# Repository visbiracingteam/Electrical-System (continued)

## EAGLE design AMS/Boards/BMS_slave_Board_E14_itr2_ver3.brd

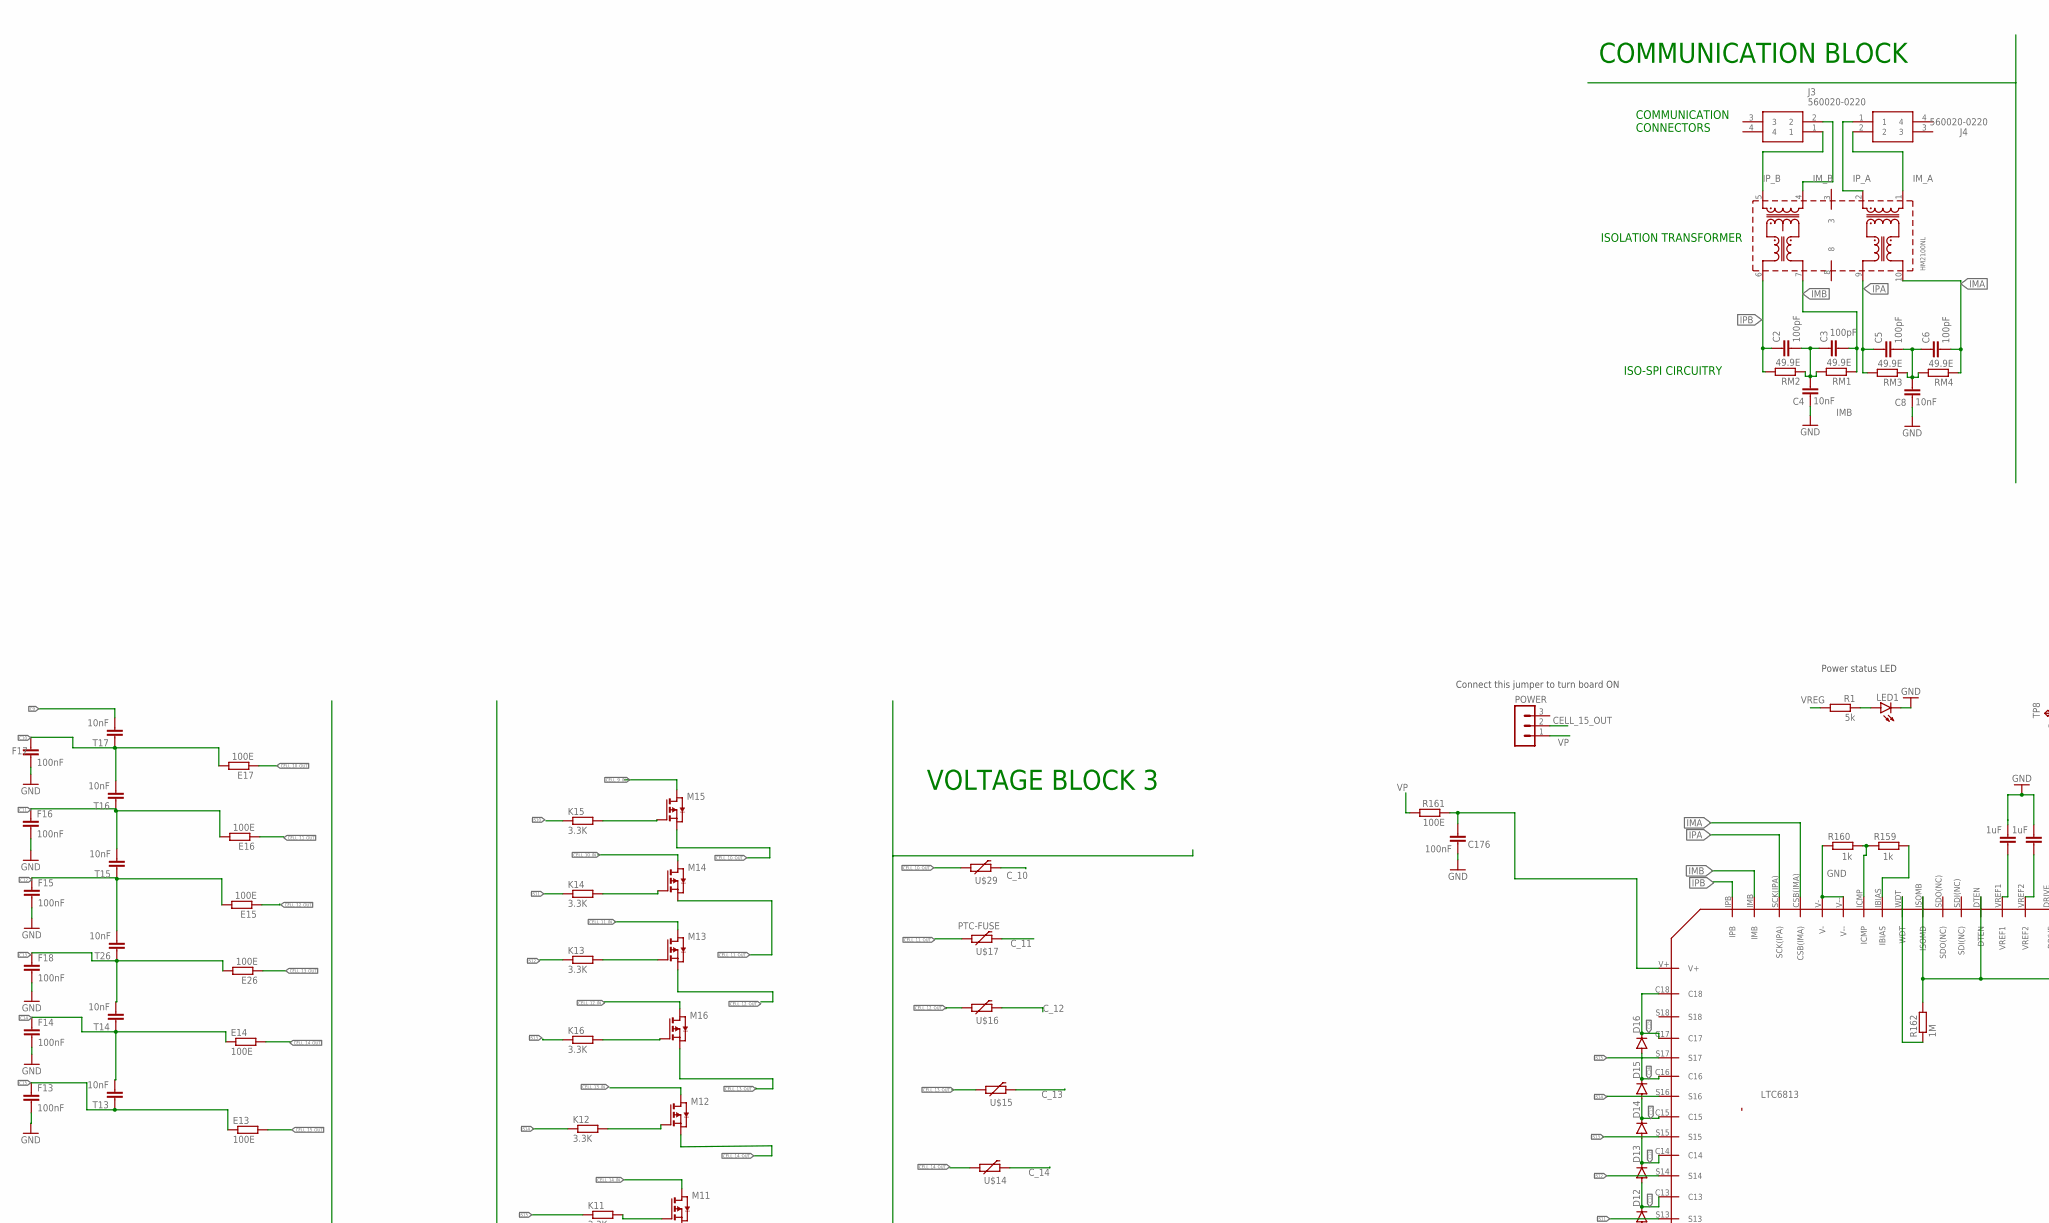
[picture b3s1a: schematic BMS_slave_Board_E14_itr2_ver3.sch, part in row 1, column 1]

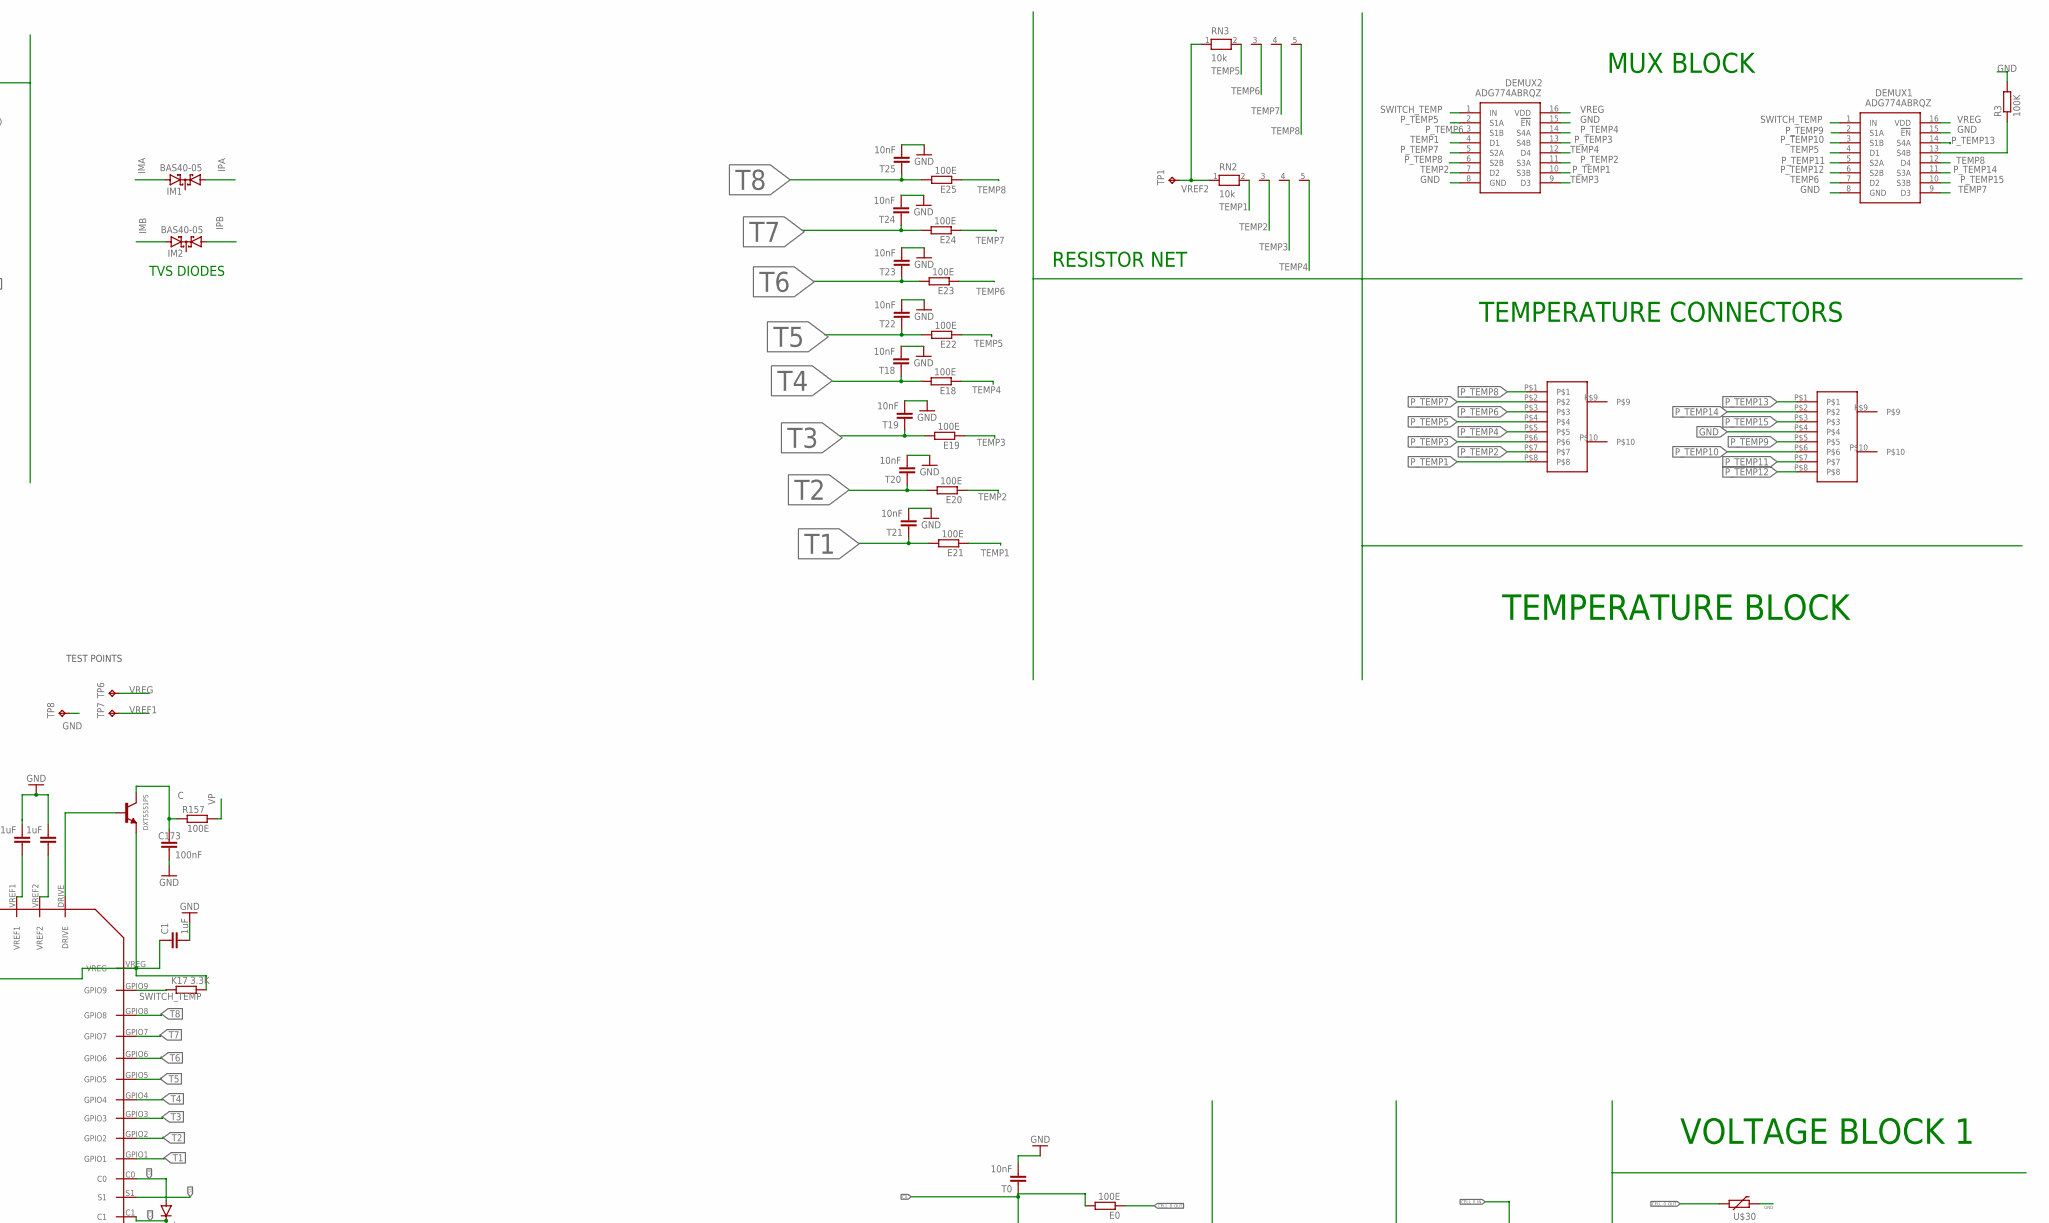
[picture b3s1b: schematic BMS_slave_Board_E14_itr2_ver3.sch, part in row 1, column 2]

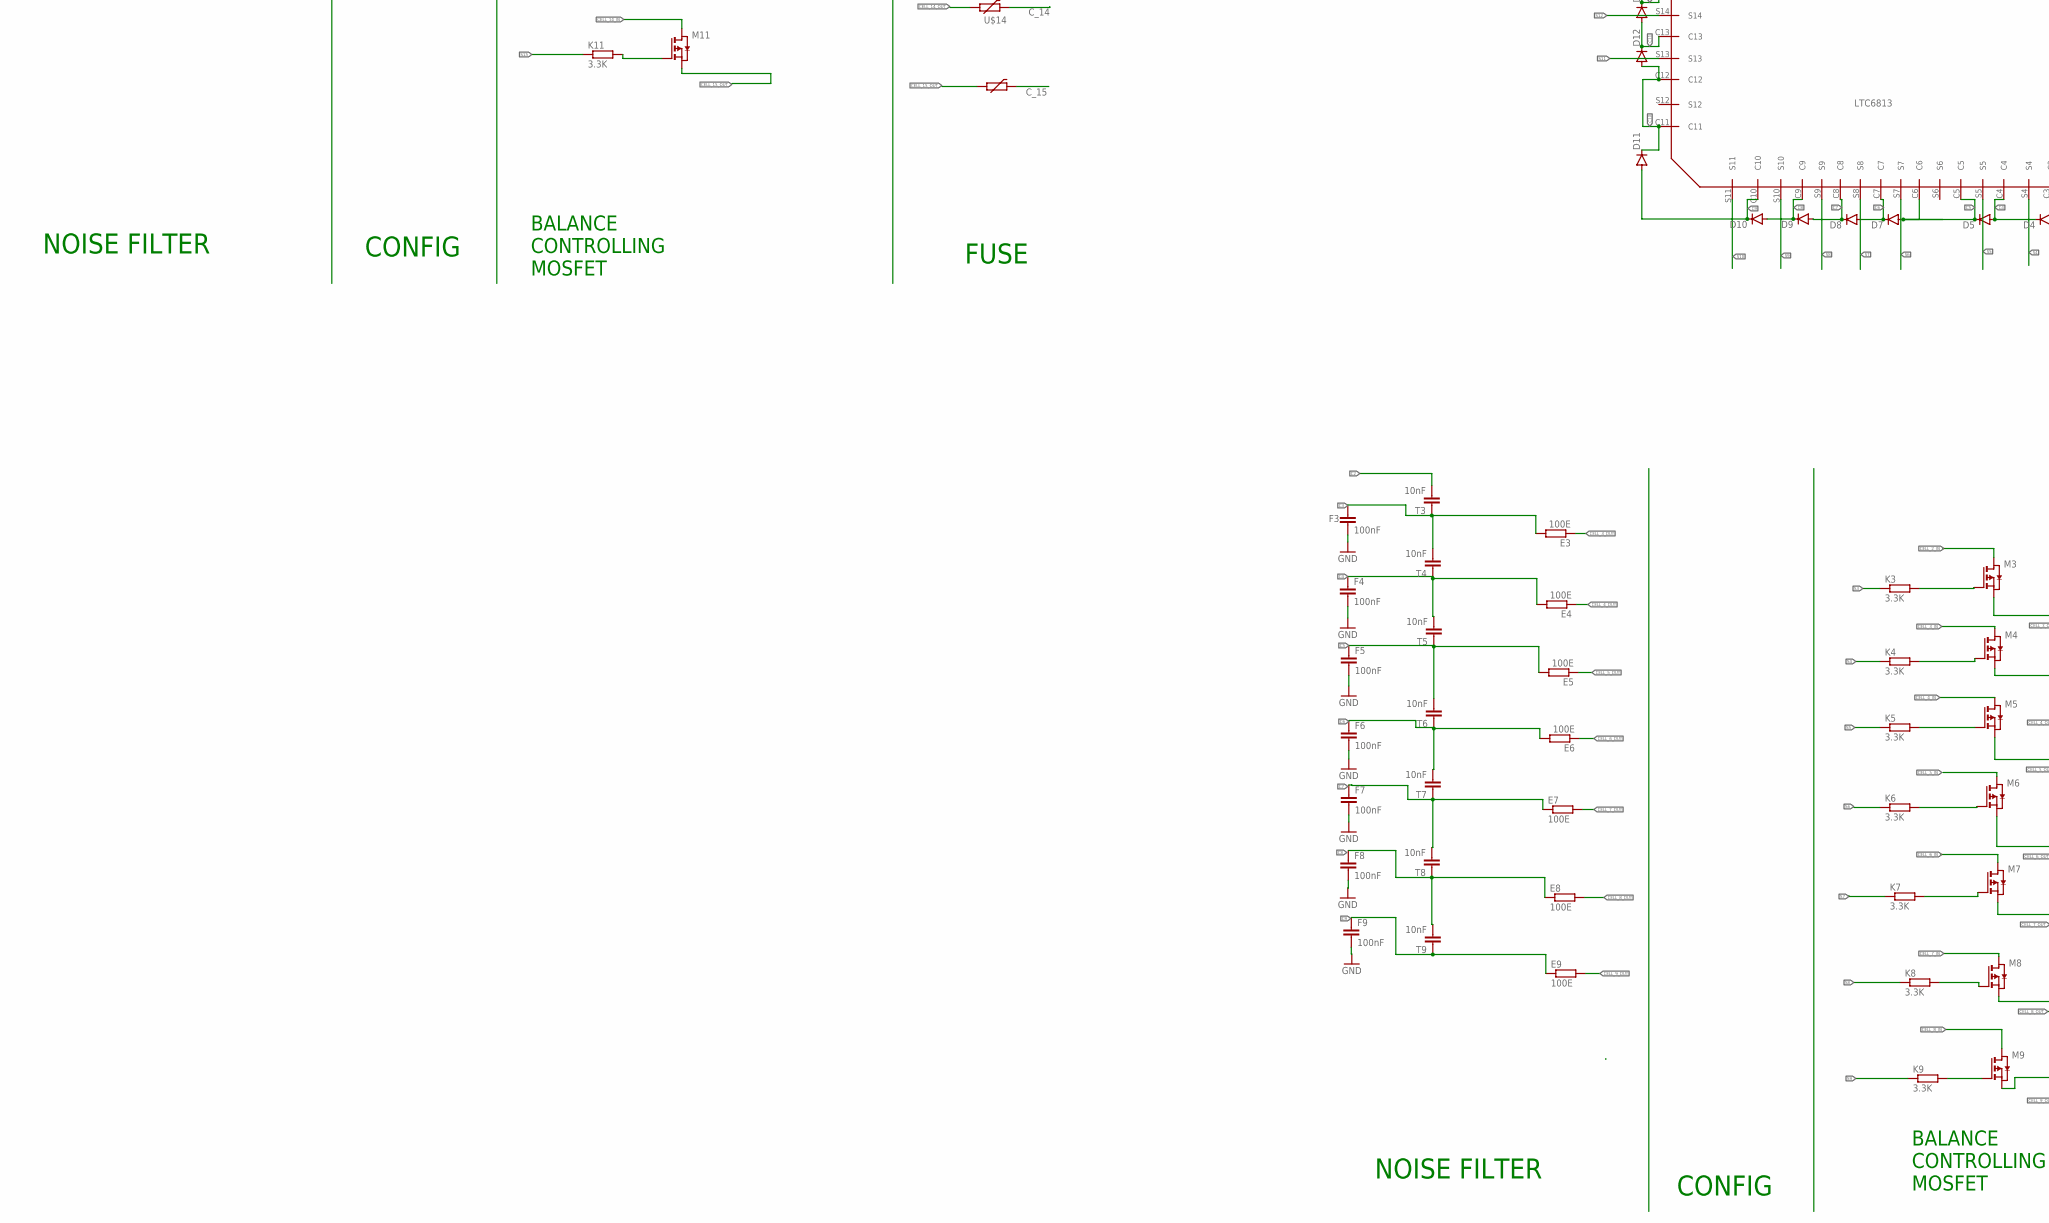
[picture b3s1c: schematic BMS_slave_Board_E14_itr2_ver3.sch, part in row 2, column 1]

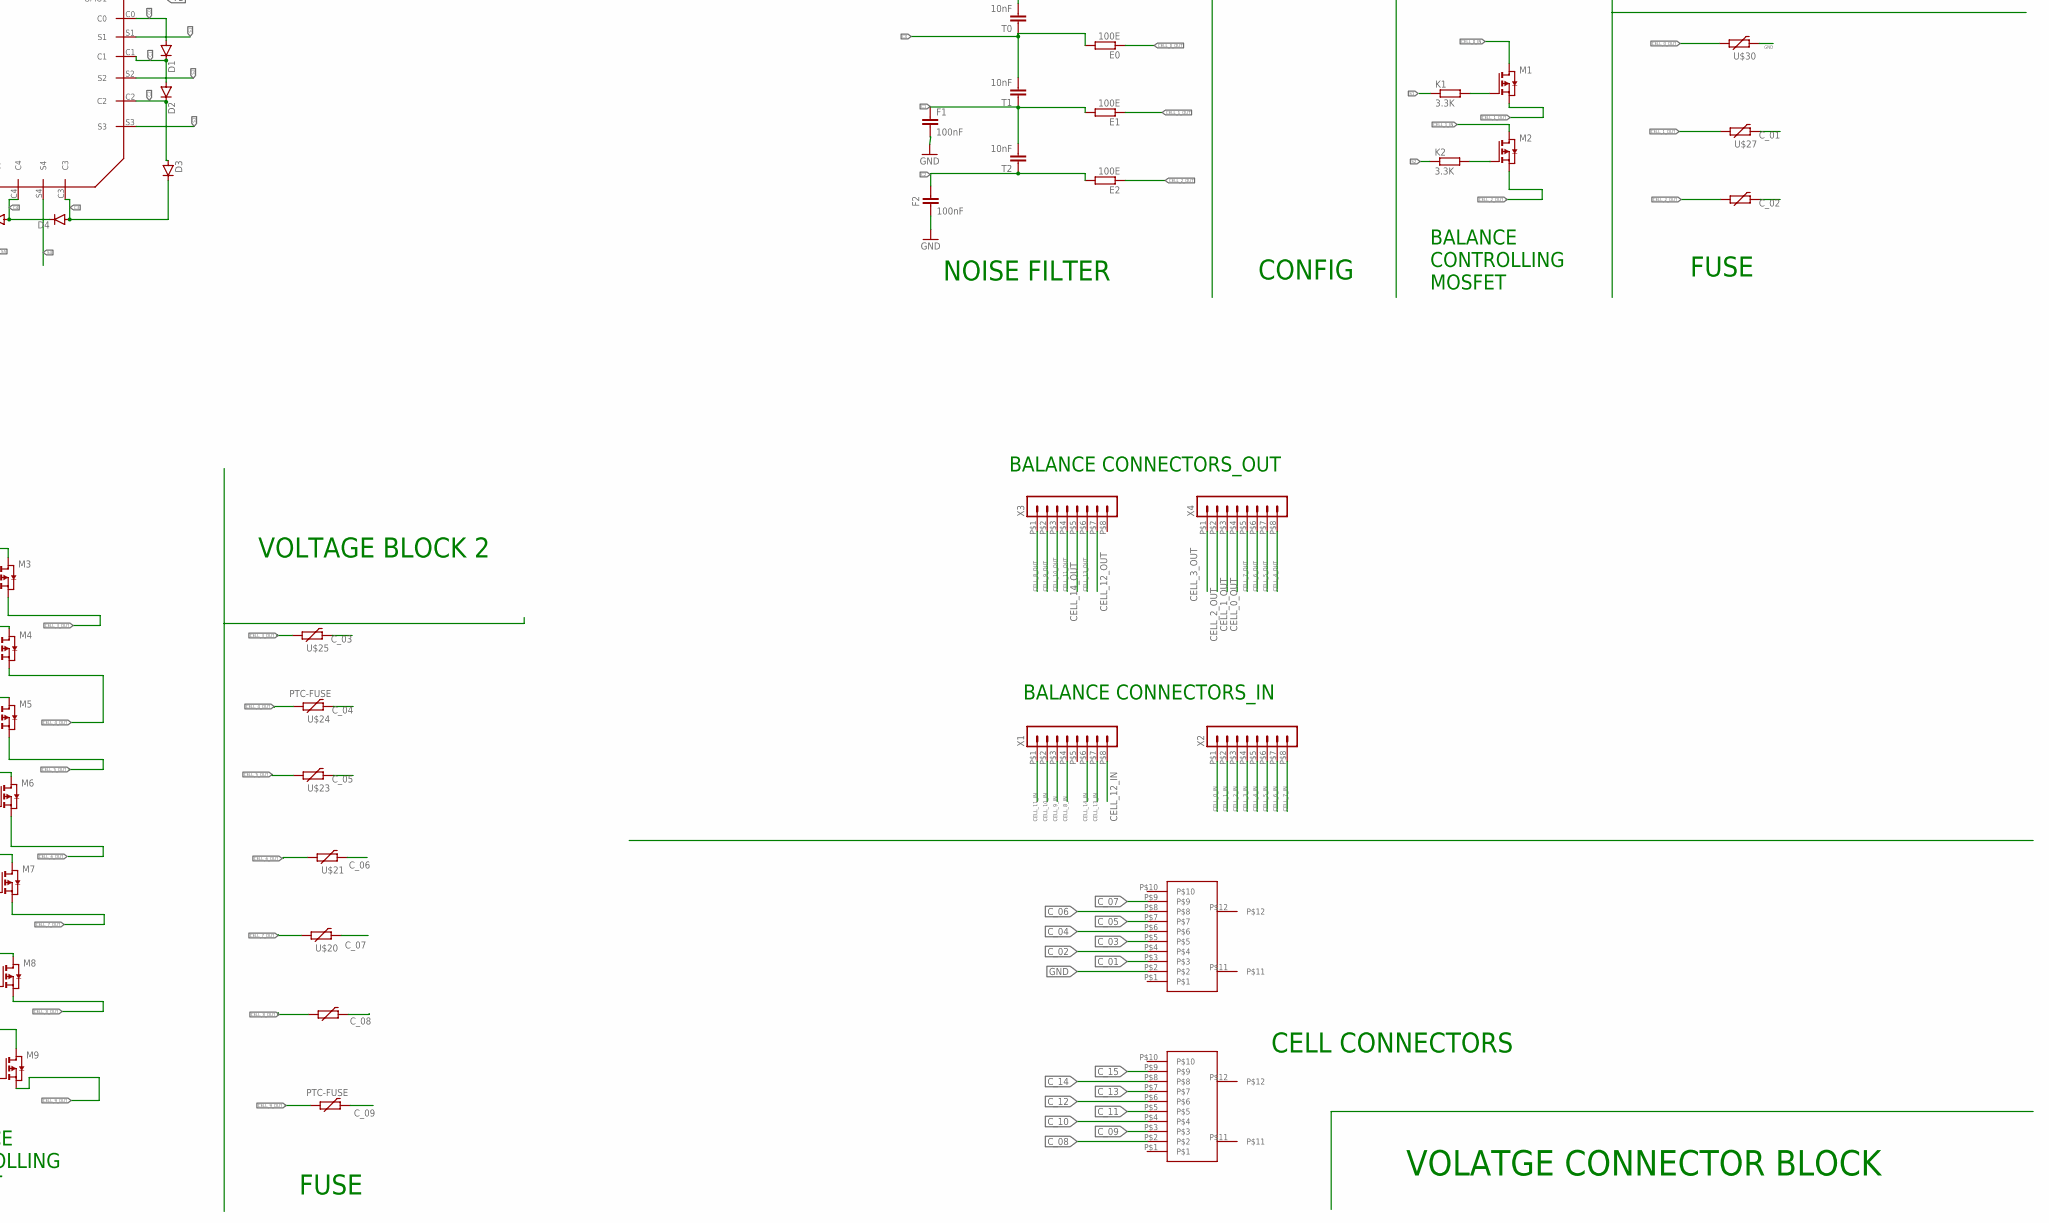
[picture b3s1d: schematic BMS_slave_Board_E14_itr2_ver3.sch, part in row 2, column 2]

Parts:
C1, C175, C177: 1uF; C0805
C2, C3, C5, C6: 100pF; C0603
C4, C8: 10nF; C0603
C173, C176: 100nF; C0805
D1, D2, D3, D4, D5, D7, D8, D9, D10, D11, D12, D13, D14, D15, D16: DIODE-SOD123; SOD123
DEMUX1, DEMUX2: ADG774ABRQZ; SOP64P600X175-16N
E0, E1, E2, E3, E4, E5, E6, E7, E8, E9, E13, E14, E15, E16, E17, E18, E19, E20, E21, E22, E23, E24, E25, E26: 100E; R0603
F1, F2, F3, F4, F5, F6, F7, F8, F9, F13, F14, F15, F16, F17, F18: 100nF; C1206
IM1, IM2: BAS40-05; SOT23
J3, J4: 560020-0220; 5600200220
K1, K2, K3, K4, K5, K6, K7, K8, K9, K11, K12, K13, K14, K15, K16, K17: 3.3K; R0603
LED1: LEDSMT1206; 1206
M1, M2, M3, M4, M5, M6, M7, M8, M9, M11, M12, M13, M14, M15, M16: PMOSSOT23; SOT-23
POWER: MA03-1
R1: 5k; R0805
R3: 100K; R0805
R157, R161: 100E; R0805
R159, R160: 1k; R0805
R162: 1M; R0805
RM1, RM2, RM3, RM4: 49.9E; R0603
RN2, RN3: 10k; RN-5
T0, T1, T2, T3, T4, T5, T6, T7, T8, T9, T13, T14, T15, T16, T17, T18, T19, T20, T21, T22, T23, T24, T25, T26: 10nF; C0603
TP1, TP6, TP7, TP8: TPPAD1-13; P1-13
U$1: HM2100NL
U$2: DXT5551P5
U$3: LTC6813
U$8, U$9: VERTICALBMS8
U$10, U$11: VERTICALBMS10
U$13, U$14, U$15, U$16, U$17, U$18, U$19, U$20, U$21, U$23, U$24, U$25, U$26, U$27, U$29, U$30: PTC-FUSE; 1206
X1, X2, X3, X4: HEADER_POS8_44914-0801; 44914-0801

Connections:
C: C173.1, R157.1, U$2.C
C0: D1.A, E0.2, T0.1, T1.2, U$3.C0
C1: D1.C, D2.A, E1.2, F1.1, T1.1, T2.2, U$3.C1
C2: D2.C, D3.A, E2.2, F2.1, T2.1, T3.2, U$3.C2
C3: D3.C, D4.A, E3.2, F3.1, T3.1, T4.2, U$3.C3
C4: D4.C, D5.A, E4.2, F4.1, T4.1, T5.2, U$3.C4
C5: D5.C, D7.A, E5.2, F5.1, T5.1, T6.2, U$3.C5, U$3.C6
C6: D7.C, D8.A, E6.2, F6.1, T6.1, T7.2, U$3.C7
C7: D8.C, D9.A, E7.1, F7.1, T7.1, T8.2, U$3.C8
C8: D9.C, D10.A, E8.1, F8.1, T8.1, T9.2, U$3.C9
C9: D10.C, D11.A, E9.1, F9.1, T9.1, T17.2, U$3.C10
C10: D11.C, D12.A, E17.2, F17.1, T16.2, T17.1, U$3.C11, U$3.C12
C11: D12.C, D13.A, E16.2, F16.1, T15.2, T16.1, U$3.C13
C12: D13.C, D14.A, E15.2, F15.1, T15.1, T26.2, U$3.C14
C13: D14.C, D15.A, E26.2, F18.1, T14.2, T26.1, U$3.C15
C14: D15.C, D16.A, E14.1, F14.1, T13.2, T14.1, U$3.C16
C15: D16.C, E13.1, F13.1, T13.1, U$3.C17, U$3.C18
CELL_0_IN: M1.1 (D), X2.P$1 (1)
CELL_0_OUT: E0.1, U$30.2, X4.P$4 (4)
CELL_1_IN: M2.1 (D), X2.P$2 (2)
CELL_1_OUT: E1.1, M1.2 (S), U$27.2, X4.P$3 (3)
CELL_2_IN: M3.1 (D), X2.P$3 (3)
CELL_2_OUT: E2.1, M2.2 (S), U$26.2, X4.P$2 (2)
CELL_3_IN: M4.1 (D), X2.P$4 (4)
CELL_3_OUT: E3.1, M3.2 (S), U$25.2, X4.P$1 (1)
CELL_4_IN: M5.1 (D), X2.P$5 (5)
CELL_4_OUT: E4.1, M4.2 (S), U$24.2, X4.P$8 (8)
CELL_5_IN: M6.1 (D), X2.P$6 (6)
CELL_5_OUT: E5.1, M5.2 (S), U$23.2, X4.P$7 (7)
CELL_6_IN: M7.1 (D), X2.P$7 (7)
CELL_6_OUT: E6.1, M6.2 (S), U$21.2, X4.P$6 (6)
CELL_7_IN: M8.1 (D), X2.P$8 (8)
CELL_7_OUT: E7.2, M7.2 (S), U$20.2, X4.P$5 (5)
CELL_8_IN: M9.1 (D), X1.P$4 (4)
CELL_8_OUT: E8.2, M8.2 (S), U$19.2, X3.P$1 (1)
CELL_9_IN: M15.1 (D), X1.P$3 (3)
CELL_9_OUT: E9.2, M9.2 (S), U$18.2, X3.P$2 (2)
CELL_10_IN: M14.1 (D), X1.P$2 (2)
CELL_10_OUT: E17.1, M15.2 (S), U$29.2, X3.P$3 (3)
CELL_11_IN: M13.1 (D), X1.P$1 (1)
CELL_11_OUT: E16.1, M14.2 (S), U$17.2, X3.P$4 (4)
CELL_12_IN: M16.1 (D), X1.P$8 (8)
CELL_12_OUT: E15.1, M13.2 (S), U$16.2, X3.P$7 (7)
CELL_13_IN: M12.1 (D), X1.P$7 (7)
CELL_13_OUT: E26.1, M16.2 (S), U$15.2, X3.P$6 (6)
CELL_14_IN: M11.1 (D), X1.P$6 (6)
CELL_14_OUT: E14.2, M12.2 (S), U$14.2, X3.P$5 (5)
CELL_15_OUT: E13.2, M11.2 (S), POWER.2, U$13.2
C_01: U$10.P$3, U$27.1
C_02: U$10.P$4, U$26.1
C_03: U$10.P$5, U$25.1
C_04: U$10.P$6, U$24.1
C_05: U$10.P$7, U$23.1
C_06: U$10.P$8, U$21.1
C_07: U$10.P$9, U$20.1
C_08: U$11.P$2, U$19.1
C_09: U$11.P$3, U$18.1
C_10: U$11.P$4, U$29.1
C_11: U$11.P$5, U$17.1
C_12: U$11.P$6, U$16.1
C_13: U$11.P$7, U$15.1
C_14: U$11.P$8, U$14.1
C_15: U$11.P$9, U$13.1
GND: C1.2, C4.1, C8.1, C173.2, C175.2, C176.2, C177.2, DEMUX1.8 (GND), DEMUX1.15 (!EN), DEMUX2.8 (GND), DEMUX2.15 (!EN), F1.2, F2.2, F3.2, F4.2, F5.2, F6.2, F7.2, F8.2, F9.2, F13.2, F14.2, F15.2, F16.2, F17.2, F18.2, LED1.C, R3.2, R160.1, T0.2, T18.2, T19.2, T20.2, T21.2, T22.2, T23.2, T24.2, T25.2, TP8.TP, U$3.V-, U$3.V--, U$9.P$4, U$10.P$2, U$30.1
IMA: C6.2, IM1.2 (A2), RM4.1, U$1.10, U$3.CSB(IMA)
IMB: C3.2, IM2.2 (A2), RM1.1, U$1.7, U$3.IMB
IM_A: J4.2, U$1.1
IM_B: J3.2, U$1.4
IPA: C5.1, IM1.1 (A1), RM3.2, U$1.9, U$3.SCK(IPA)
IPB: C2.1, IM2.1 (A1), RM2.2, U$1.6, U$3.IPB
IP_A: J4.1, U$1.2
IP_B: J3.1, U$1.5
unnamed: C2.2, C3.1, C4.2, RM1.2, RM2.1
unnamed: C5.2, C6.1, C8.2, RM3.1, RM4.2
unnamed: R162.1, U$3.WDT
unnamed: DEMUX1.13 (S4B), R3.1
unnamed: R159.1, R160.2, U$3.ICMP
unnamed: K1.2, M1.3 (G)
unnamed: K2.2, M2.3 (G)
unnamed: K3.2, M3.3 (G)
unnamed: K4.2, M4.3 (G)
unnamed: K5.2, M5.3 (G)
unnamed: K6.2, M6.3 (G)
unnamed: K7.2, M7.3 (G)
unnamed: K16.2, M16.3 (G)
unnamed: K8.2, M8.3 (G)
unnamed: K9.2, M9.3 (G)
unnamed: K12.2, M12.3 (G)
unnamed: K15.2, M15.3 (G)
unnamed: K14.2, M14.3 (G)
unnamed: K13.2, M13.3 (G)
unnamed: K11.2, M11.3 (G)
unnamed: U$2.B, U$3.DRIVE
unnamed: R159.2, U$3.IBIAS
unnamed: C176.1, R161.1, U$3.V+
P_TEMP1: DEMUX2.10 (S3B), U$8.P$8
P_TEMP2: DEMUX2.11 (S3A), U$8.P$7
P_TEMP3: DEMUX2.13 (S4B), U$8.P$6
P_TEMP4: DEMUX2.14 (S4A), U$8.P$5
P_TEMP5: DEMUX2.2 (S1A), U$8.P$4
P_TEMP6: DEMUX2.3 (S1B), U$8.P$3
P_TEMP7: DEMUX2.5 (S2A), U$8.P$2
P_TEMP8: DEMUX2.6 (S2B), U$8.P$1
P_TEMP9: DEMUX1.2 (S1A), U$9.P$5
P_TEMP10: DEMUX1.3 (S1B), U$9.P$6
P_TEMP11: DEMUX1.5 (S2A), U$9.P$7
P_TEMP12: DEMUX1.6 (S2B), U$9.P$8
P_TEMP13: DEMUX1.14 (S4A), U$9.P$1
P_TEMP14: DEMUX1.11 (S3A), U$9.P$2
P_TEMP15: DEMUX1.10 (S3B), U$9.P$3
R: LED1.A, R1.1
S1: K1.1, U$3.S1
S2: K2.1, U$3.S2
S3: K3.1, U$3.S3
S4: K4.1, U$3.S4
S5: K5.1, U$3.S5
S6: K6.1, U$3.S7
S7: K7.1, U$3.S8
S8: K8.1, U$3.S9
S9: K9.1, U$3.S10
S10: K15.1, U$3.S11
S11: K14.1, U$3.S13
S12: K13.1, U$3.S14
S13: K16.1, U$3.S15
S14: K12.1, U$3.S16
S15: K11.1, U$3.S17
SWITCH_TEMP: DEMUX1.1 (IN), DEMUX2.1 (IN), K17.1, U$3.GPIO9
T1: E21.2, T21.1, U$3.GPIO1
T2: E20.2, T20.1, U$3.GPIO2
T3: E19.2, T19.1, U$3.GPIO3
T4: E18.2, T18.1, U$3.GPIO4
T5: E22.2, T22.1, U$3.GPIO5
T6: E23.2, T23.1, U$3.GPIO6
T7: E24.2, T24.1, U$3.GPIO7
T8: E25.2, T25.1, U$3.GPIO8
TEMP1: DEMUX2.4 (D1), E21.1, RN2.2
TEMP2: DEMUX2.7 (D2), E20.1, RN2.3
TEMP3: DEMUX2.9 (D3), E19.1, RN2.4
TEMP4: DEMUX2.12 (D4), E18.1, RN2.5
TEMP5: DEMUX1.4 (D1), E22.1, RN3.2
TEMP6: DEMUX1.7 (D2), E23.1, RN3.3
TEMP7: DEMUX1.9 (D3), E24.1, RN3.4
TEMP8: DEMUX1.12 (D4), E25.1, RN3.5
VP: POWER.1, R157.2, R161.2
VREF1: C175.1, TP7.TP, U$3.VREF1
VREF2: C177.1, RN2.1, RN3.1, TP1.TP, U$3.VREF2
VREG: C1.1, DEMUX1.16 (VDD), DEMUX2.16 (VDD), K17.2, R1.2, R162.2, TP6.TP, U$2.E, U$3.DTEN, U$3.ISOMB (ISOMD), U$3.VREG

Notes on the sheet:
Power status LED
MUX BLOCK
TEMPERATURE BLOCK
RESISTOR NET
TEMPERATURE CONNECTORS
TVS DIODES
ISOLATION TRANSFORMER
COMMUNICATION CONNECTORS
ISO-SPI CIRCUITRY
COMMUNICATION BLOCK
VOLATGE CONNECTOR BLOCK
CELL CONNECTORS
BALANCE CONNECTORS_OUT
BALANCE CONNECTORS_IN
VOLTAGE BLOCK 1
FUSE
BALANCE CONTROLLING MOSFET
CONFIG
NOISE FILTER
VOLTAGE BLOCK 2
VOLTAGE BLOCK 3
Connect this jumper to turn board ON
TEST POINTS

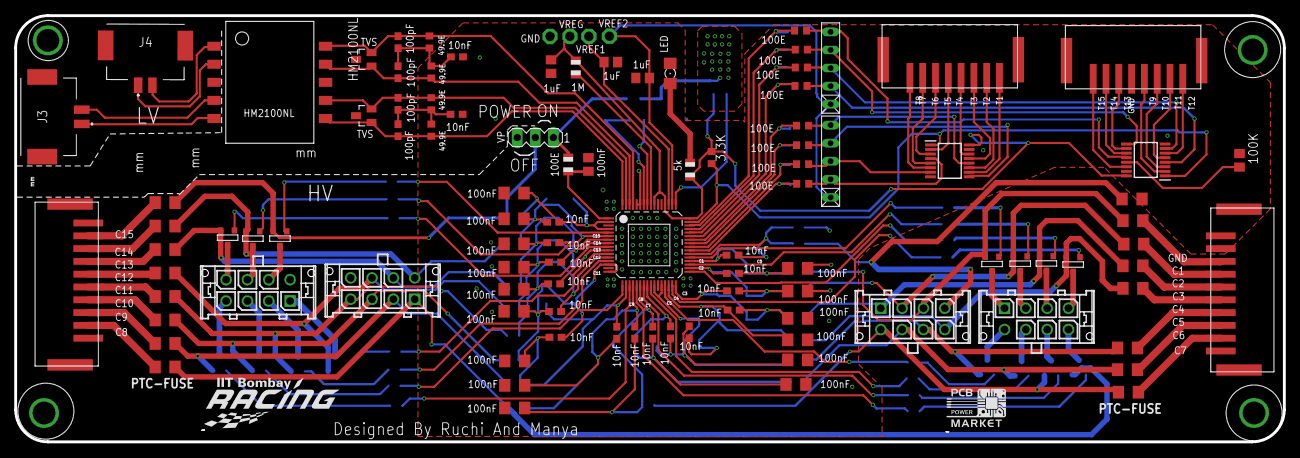
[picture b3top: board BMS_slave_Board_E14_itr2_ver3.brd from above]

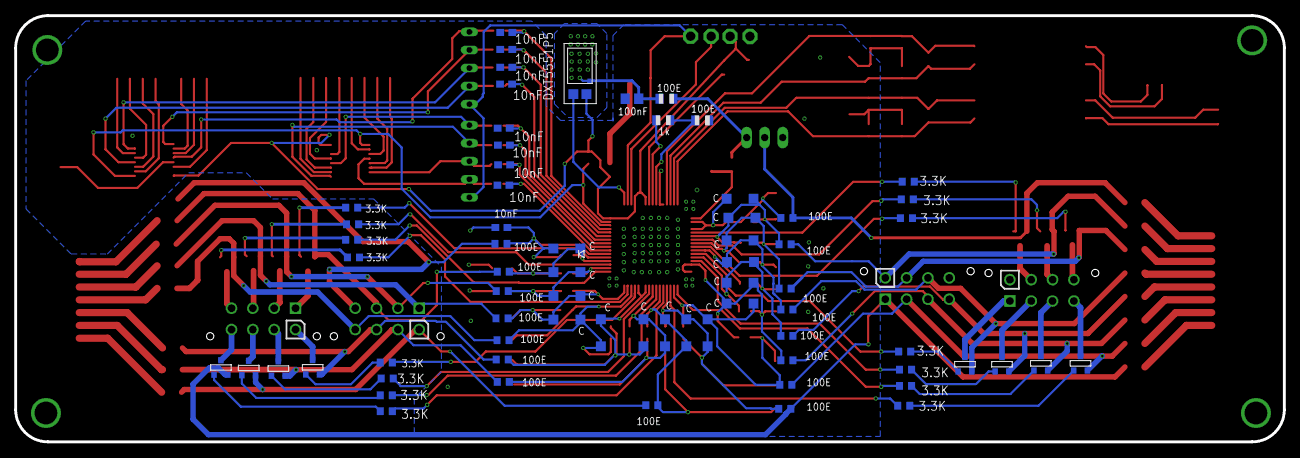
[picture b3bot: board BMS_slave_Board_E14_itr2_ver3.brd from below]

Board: 2 copper layers, 178.4 x 59.9 mm, 174 parts (68 on the bottom side), 147 nets.

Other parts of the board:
U$5: RACING_LOGO_290MIL
U$6: 330X210

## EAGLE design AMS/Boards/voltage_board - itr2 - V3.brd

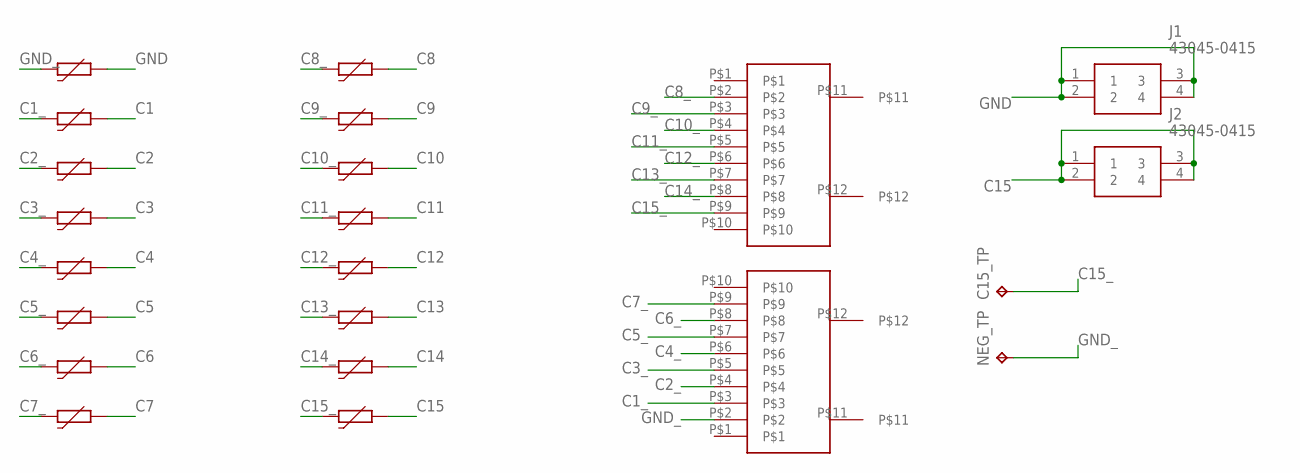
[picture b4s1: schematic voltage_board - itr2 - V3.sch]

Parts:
C15_TP: TPPAD1-13; P1-13
GND_F, GND_F1, GND_F2, GND_F3, GND_F4, GND_F5, GND_F6, GND_F7, GND_F8, GND_F9, GND_F10, GND_F11, GND_F12, GND_F13, GND_F14, GND_F15: PTC-FUSE; 1206
J1, J2: 43045-0415; 43045-04YY_15,16,17
NEG_TP: TPPAD1-13; P1-13
U$37, U$38: VERTICALBMS10

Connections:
C1: GND_F1.2
C1_: GND_F1.1, U$37.P$3
C2: GND_F2.2
C2_: GND_F2.1, U$37.P$4
C3: GND_F3.2
C3_: GND_F3.1, U$37.P$5
C4: GND_F4.2
C4_: GND_F4.1, U$37.P$6
C5: GND_F5.2
C5_: GND_F5.1, U$37.P$7
C6: GND_F6.2
C6_: GND_F6.1, U$37.P$8
C7: GND_F7.2
C7_: GND_F7.1, U$37.P$9
C8: GND_F8.2
C8_: GND_F8.1, U$38.P$2
C9: GND_F9.2
C9_: GND_F9.1, U$38.P$3
C10: GND_F10.2
C10_: GND_F10.1, U$38.P$4
C11: GND_F11.2
C11_: GND_F11.1, U$38.P$5
C12: GND_F12.2
C12_: GND_F12.1, U$38.P$6
C13: GND_F13.2
C13_: GND_F13.1, U$38.P$7
C14: GND_F14.2
C14_: GND_F14.1, U$38.P$8
C15: GND_F15.2, J2.1, J2.2, J2.3, J2.4
C15_: C15_TP.TP, GND_F15.1, U$38.P$9
GND: GND_F.2, J1.1, J1.2, J1.3, J1.4
GND_: GND_F.1, NEG_TP.TP, U$37.P$2

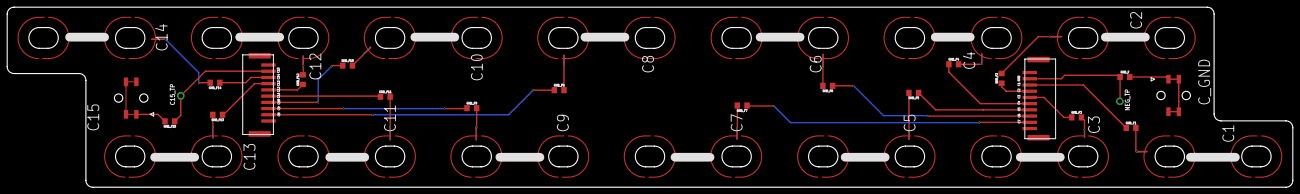
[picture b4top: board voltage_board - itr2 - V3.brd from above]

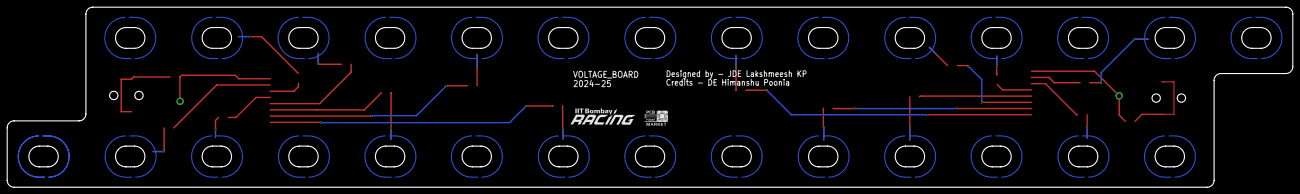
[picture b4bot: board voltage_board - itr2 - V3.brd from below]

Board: 2 copper layers, 372.0 x 52.1 mm, 24 parts (2 on the bottom side), 18 nets.

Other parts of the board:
U$8: LOGO_PCBPOWER; 270X170
U$23: IITBR_LOGO_180DIFF

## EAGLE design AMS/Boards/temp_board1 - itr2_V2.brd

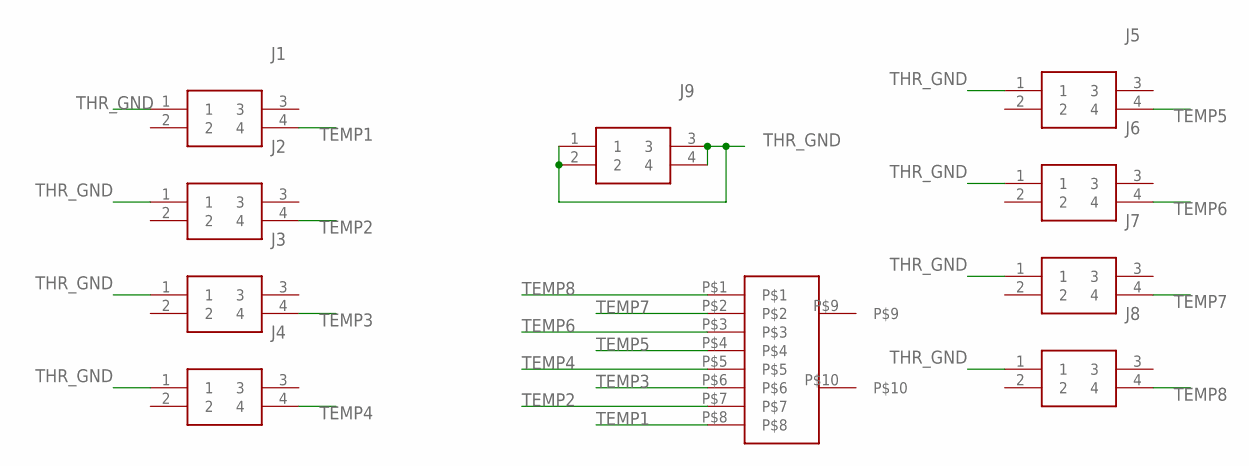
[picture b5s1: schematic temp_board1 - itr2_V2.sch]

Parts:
J1, J2, J3, J4, J5, J6, J7, J8, J9: 43045-0415; 43045-04YY_15,16,17
U$35: VERTICALBMS8

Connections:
TEMP1: J1.4, U$35.P$8
TEMP2: J2.4, U$35.P$7
TEMP3: J3.4, U$35.P$6
TEMP4: J4.4, U$35.P$5
TEMP5: J5.4, U$35.P$4
TEMP6: J6.4, U$35.P$3
TEMP7: J7.4, U$35.P$2
TEMP8: J8.4, U$35.P$1
THR_GND: J1.1, J2.1, J3.1, J4.1, J5.1, J6.1, J7.1, J8.1, J9.1, J9.2, J9.3, J9.4

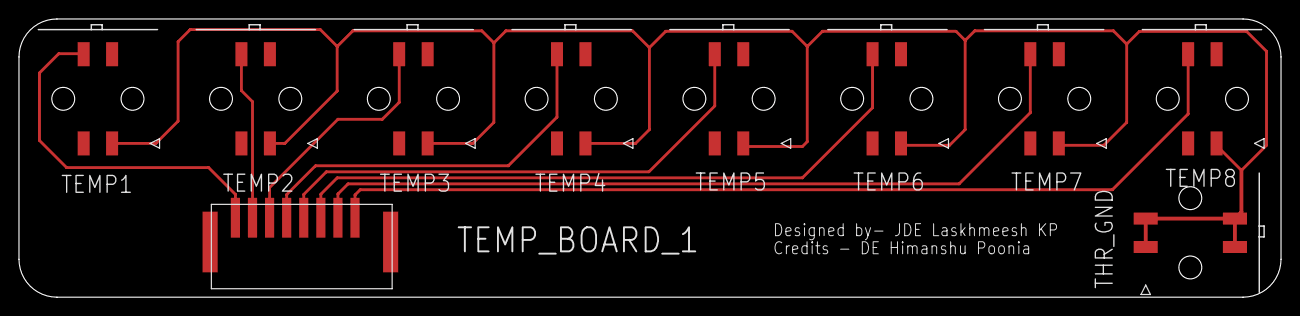
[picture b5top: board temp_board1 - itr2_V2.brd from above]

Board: 2 copper layers, 133.0 x 29.3 mm, 12 parts (2 on the bottom side), 9 nets.

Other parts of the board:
U$8: LOGO_PCBPOWER; 270X170
U$23: IITBR_LOGO_180DIFF

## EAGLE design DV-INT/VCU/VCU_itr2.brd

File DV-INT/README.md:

# DV-INT
### Contains all the files related to Driverless-Integration

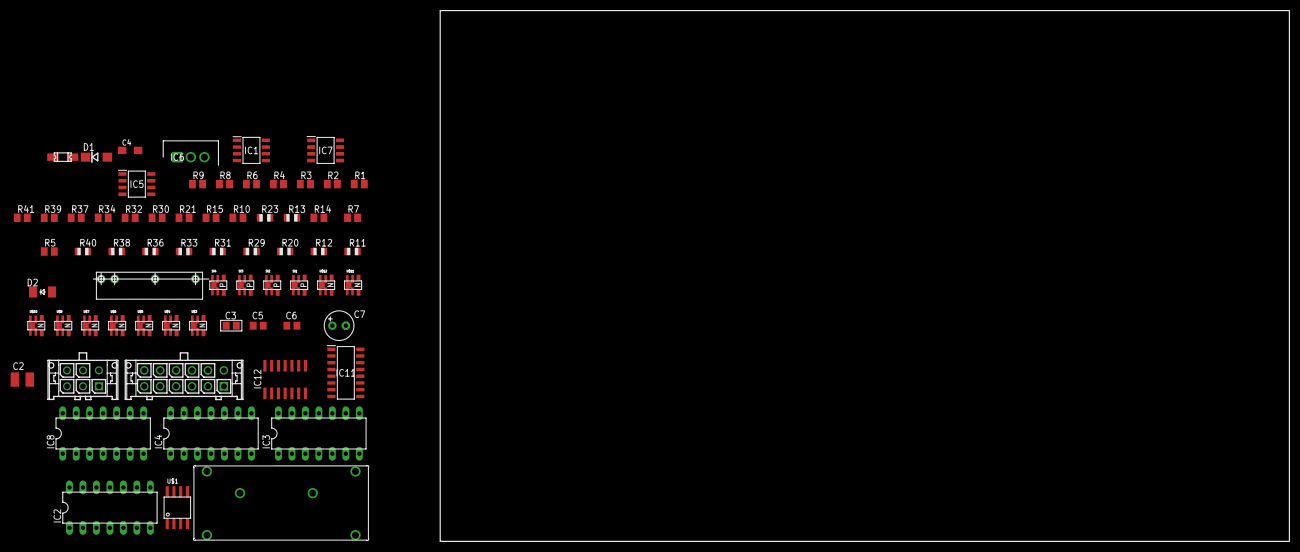
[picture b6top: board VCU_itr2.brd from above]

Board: 2 copper layers, 160.0 x 100.0 mm, 67 parts (0 on the bottom side), 54 nets, no tracks yet.

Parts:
BMS-CONN7: 43045-0612
C2: 0.01uf; C1210
C3: 1uF; C0805
C4: 1uF; SMC_A
C5: 0.1uF; C0805
C6: 0.33uF; C0805
C7: 2uF; E2,5-6
D1: DO214AC
D2: CGRM400-G; SOD-123_MINI-SMA
FUSE_1A1: 1206L
IC1: UCC2946D; SOIC127P600X175-8N
IC2, IC4, IC8: 4081N; DIL14
IC3: 4071N; DIL14
IC5, IC7: SI4425FDY-T1-GE3; SOIC127P600X175-8N
IC6: L7805CV-DG; TO255P460X1020X2008-3P
IC11: 74HC238D; SOIC127P600X175-16N
IC12: LM324D; SO14
R1: 51k; M0805
R2, R3, R4, R6, R8, R9, R10, R15, R21, R30, R32, R34, R37, R39, R41: 10k; M0805
R5, R7, R14: 100k; M0805
R11, R12, R20, R29, R31, R33, R36, R38, R40: 100k; R0805
R13, R23: 10k; R0805
SI1, SI2, SI3, SI4: TSOP-6_PMOS
U$1: NCV2903; SOIC-8
U$2: G6DN_RELAY
U$3, U$4, U$5, U$6, U$7, U$8, U$10, U$11, U$12: TSOP-6_NMOS
U$9: SFM_RELAY
X2: 44914-1201

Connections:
2V_REF: R1.1, R2.2, U$1.2, U$1.5
3V3: IC11.6, IC11.16
+5V: C5.1, IC6.3
+12V: C6.1, C7.+, IC2.14, IC3.14, IC4.14, IC5.1, IC5.2, IC5.3, IC6.1, IC7.1, IC7.2, IC7.3, IC8.14, R1.2, R5.1, R7.1, R8.1, R9.1, R13.2, R14.1, R23.2, SI1.S, SI2.S, SI3.S, SI4.S, U$1.8, U$5.1, U$5.2, U$5.5, U$5.6, U$5.D, U$6.1, U$6.2, U$6.5, U$6.6, U$6.D, U$7.1, U$7.2, U$7.5, U$7.6, U$7.D, U$8.1, U$8.2, U$8.5, U$8.6, U$8.D, U$10.1, U$10.2, U$10.5, U$10.6, U$10.D, U$11.1, U$11.2, U$11.5, U$11.6, U$11.D, U$12.1, U$12.2, U$12.5, U$12.6, U$12.D, X2.P$11
+12V_AS: C2.2, D1.C, U$9.NO+, U$9.V+, X2.P$9
+12V_IN: C4.+, FUSE_1A1.P$1
ACCELERATION: R20.1, R21.2, U$5.S
ACCELERATION_IN: IC11.15, R20.2, U$5.G
ASMS_STATE: IC2.2, IC4.6, R5.2, SI2.G, U$9.NO-, X2.P$10
ASMS_STATE_INV: IC4.2, IC4.8, R6.2, SI2.1, SI2.2, SI2.5, SI2.6, SI2.D
AS_LOGIC: C3.2, D2.C, IC3.3, U$2.P$1
AUTOCROSS: R38.1, R39.2, U$11.S
AUTOCROSS_IN: IC11.13, R38.2, U$11.G
BLUE_LED: IC7.5, IC7.6, IC7.7, IC7.8, R4.2, X2.P$5
EBS_TEST: R31.1, R32.2, U$7.S, X2.P$7
EBS_TEST_IN: IC11.11, R31.2, U$7.G
FROM_IMD: U$2.P$4, X2.P$3
GND: C2.1, C3.1, C4.-, C5.2, C6.2, C7.-, D1.A, D2.A, IC1.1, IC2.7, IC3.7, IC4.7, IC6.2, IC8.7, IC11.4, IC11.5, IC11.8, IC12.11, R2.1, R3.1, R4.1, R6.1, R10.1, R11.1, R12.1, R15.1, R21.1, R30.1, R32.1, R34.1, R37.1, R39.1, R41.1, SI1.G, U$1.4, U$2.P$2, U$3.S, U$4.S, U$9.V-, X2.P$12
HV_RESET: BMS-CONN7.P$1, IC3.4
HV_RESET_CP: BMS-CONN7.P$2, IC4.1
HV_RESET_SP: BMS-CONN7.P$3, IC4.5
IN1: IC11.1, IC12.1, IC12.2
IN2: IC11.2, IC12.6, IC12.7
IN3: IC11.3, IC12.8, IC12.9
INSPECTION: R33.1, R34.2, U$8.S
INSPECTION_IN: IC11.10, R33.2, U$8.G
MANUAL_DRIVING: IC4.9, R7.2, R40.1, R41.2, SI3.G, U$12.S
MANUAL_DRIVING_IN: IC11.9, R40.2, U$12.G
MANUAL_DRIVING_INV: IC2.12, R10.2, SI3.1, SI3.2, SI3.5, SI3.6, SI3.D
MANUAL_VALVE: IC2.6, R14.2, SI4.G, X2.P$8
MANUAL_VALVE_INV: IC4.12, R15.2, SI4.1, SI4.2, SI4.5, SI4.6, SI4.D
MISSION_SET: IC4.13, R12.2, U$4.G
MISSION_SET_12V: IC2.5, R13.1, U$4.1, U$4.2, U$4.5, U$4.6, U$4.D
unnamed: IC7.4, R8.2, U$1.7
unnamed: IC2.3, IC2.8
unnamed: IC5.4, R9.2, U$1.1
unnamed: IC4.10, IC8.1
unnamed: IC2.4, IC2.9
unnamed: IC4.11, IC8.2
unnamed: IC2.11, IC3.1
unnamed: FUSE_1A1.P$2, SI1.1, SI1.2, SI1.5, SI1.6, SI1.D
RES_1_IN: U$2.P$3, U$9.NC+, X2.P$1
RES_1_OUT: U$9.NC-, X2.P$2
SIG1: IC2.10, IC2.13
SIG2: IC3.5, IC4.3
SIG3: IC3.6, IC4.4
SIG4: IC3.2, IC8.3
SKIDPAD: R29.1, R30.2, U$6.S
SKIDPAD_IN: IC11.14, R29.2, U$6.G
TRACKDRIVE: R36.1, R37.2, U$10.S, X2.P$6
TRACKDRIVE_IN: IC11.12, R36.2, U$10.G
WATCHDOG_OUT: IC1.5, R11.2, U$3.G
WATCHDOG_OUT_12V: IC2.1, R23.1, U$3.1, U$3.2, U$3.5, U$3.6, U$3.D
YELLOW_LED: IC5.5, IC5.6, IC5.7, IC5.8, R3.2, X2.P$4

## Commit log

2024-10-06 testing pcb version control
2024-10-06 iteration2
2024-10-07 Create ecu
2024-10-07 commit message
2024-10-07 commit delete
2024-10-07 folder test
2024-10-07 RDN test
2024-10-07 CCD organised
2024-10-07 re-organising
2024-10-07 adding README.md
2024-10-07 add README.md
2024-10-07 adding gitignore
2024-10-07 testing webhoob
2024-10-08 VCU and DAN schematics
2024-10-08 / BOARDS
2024-10-08 Boards/
2024-10-08 Create description
2024-10-08 Create FINAL_FSA_CODE
2024-10-08 test code for ams
